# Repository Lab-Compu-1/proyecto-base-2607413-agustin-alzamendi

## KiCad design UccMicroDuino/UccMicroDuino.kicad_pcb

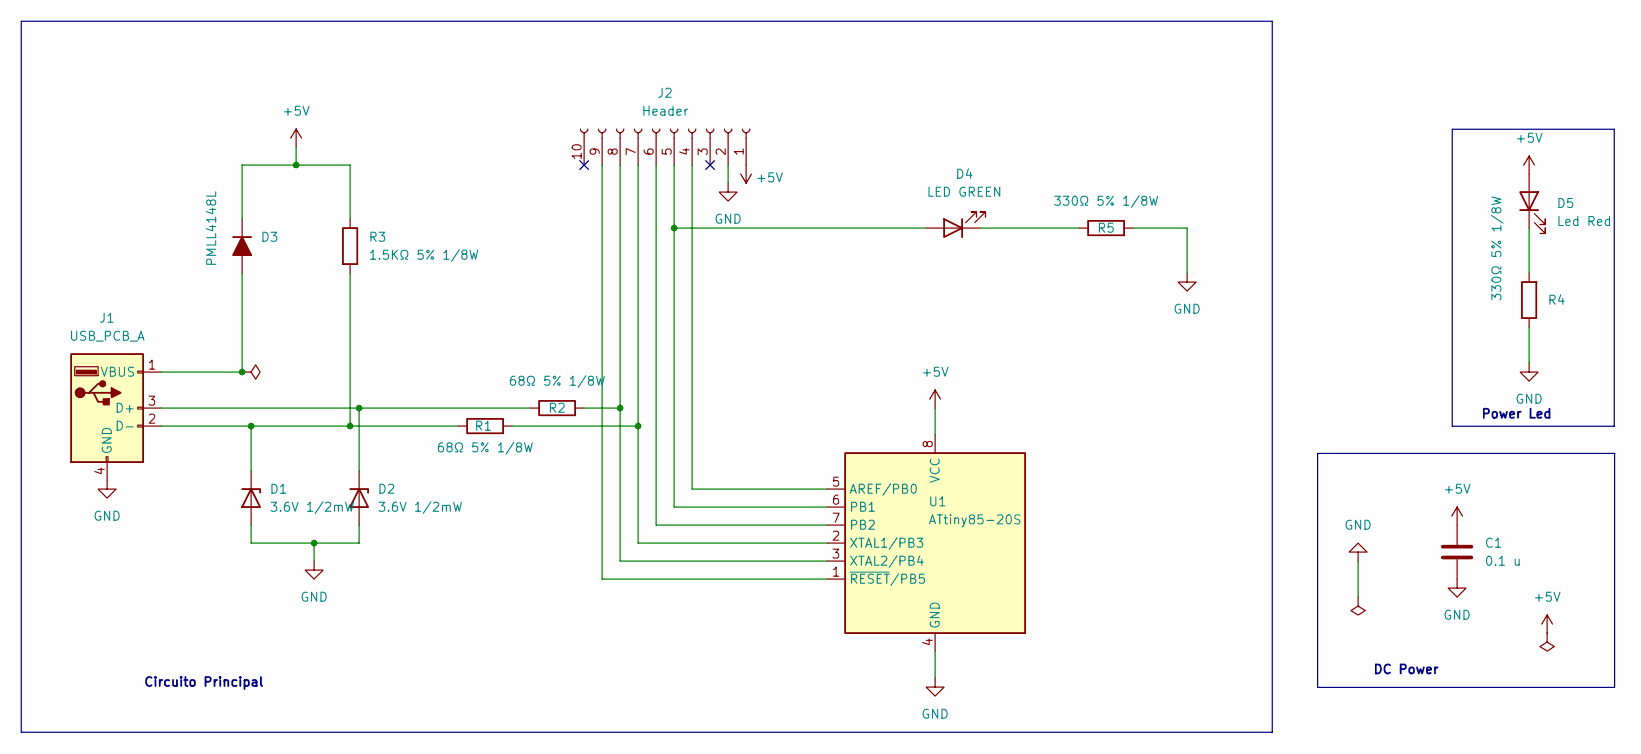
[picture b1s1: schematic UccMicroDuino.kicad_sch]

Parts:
C1: 0.1 u; C_0805_2012Metric_Pad1.18x1.45mm_HandSolder
D1, D2: 3.6V 1/2mW; D_SOD-123
D3: PMLL4148L; D_MiniMELF
D4: LED GREEN; ledSMD
D5: Led Red; ledSMD
J1: USB_PCB_A; USB_A_UCC
J2: Header; PinHeader_1x10_P2.54mm_Vertical
R1, R2: 68Ω 5% 1/8W; R_0805_2012Metric_Pad1.20x1.40mm_HandSolder
R3: 1.5KΩ 5% 1/8W; R_0805_2012Metric_Pad1.20x1.40mm_HandSolder
R4, R5: 330Ω 5% 1/8W; R_0805_2012Metric_Pad1.20x1.40mm_HandSolder
U1: ATtiny85-20S; SOIC-8_5.3x5.3mm_P1.27mm

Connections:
+5V: C1.1, D3.1 (K), D5.2 (A), J2.1, R3.1, U1.8 (VCC)
GND: C1.2, D1.2 (A), D2.2 (A), J1.4 (GND), J2.2, R4.1, R5.2, U1.4 (GND)
unnamed: D1.1 (K), J1.2 (D-), R1.1, R3.2
unnamed: D2.1 (K), J1.3 (D+), R2.1
unnamed: D3.2 (A), J1.1 (VBUS)
unnamed: D4.2 (A), J2.5, U1.6 (PB1)
unnamed: D4.1 (K), R5.1
unnamed: D5.1 (K), R4.2
unnamed: J2.4, U1.5 (AREF/PB0)
unnamed: J2.6, U1.7 (PB2)
unnamed: J2.7, R1.2, U1.2 (XTAL1/PB3)
unnamed: J2.8, R2.2, U1.3 (XTAL2/PB4)
unnamed: J2.9, U1.1 (~RESET/PB5)

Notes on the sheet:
Power Led
Circuito Principal
DC Power

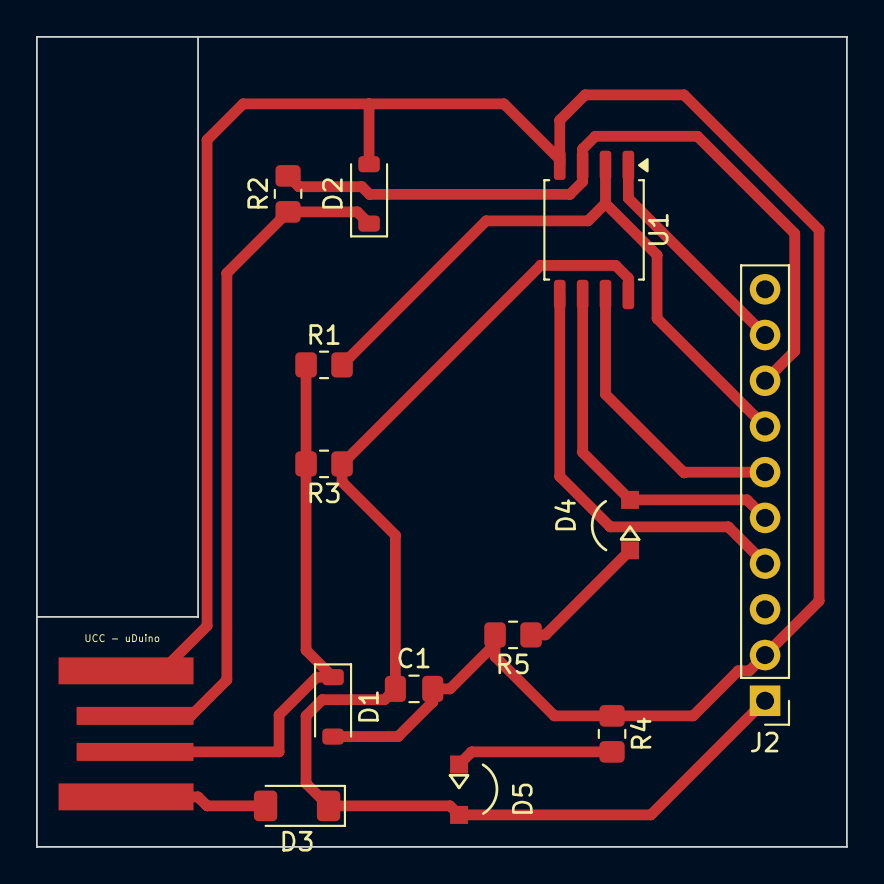
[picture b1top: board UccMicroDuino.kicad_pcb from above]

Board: 2 copper layers, 45.0 x 45.0 mm, 14 parts (0 on the bottom side), 13 nets.

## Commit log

2026-03-30 GitHub Classroom Feedback
2026-03-30 Setting up GitHub Classroom Feedback
2026-05-18 2607413-mi primer versionado con gitBash
2026-05-26 mi primer versionado con gitBash
2026-05-26 PCB finalizado
2026-05-26 Agregue .gitignore
2026-05-26 Cambio en el esquematico
2026-05-31 Realice pequeño cambio
